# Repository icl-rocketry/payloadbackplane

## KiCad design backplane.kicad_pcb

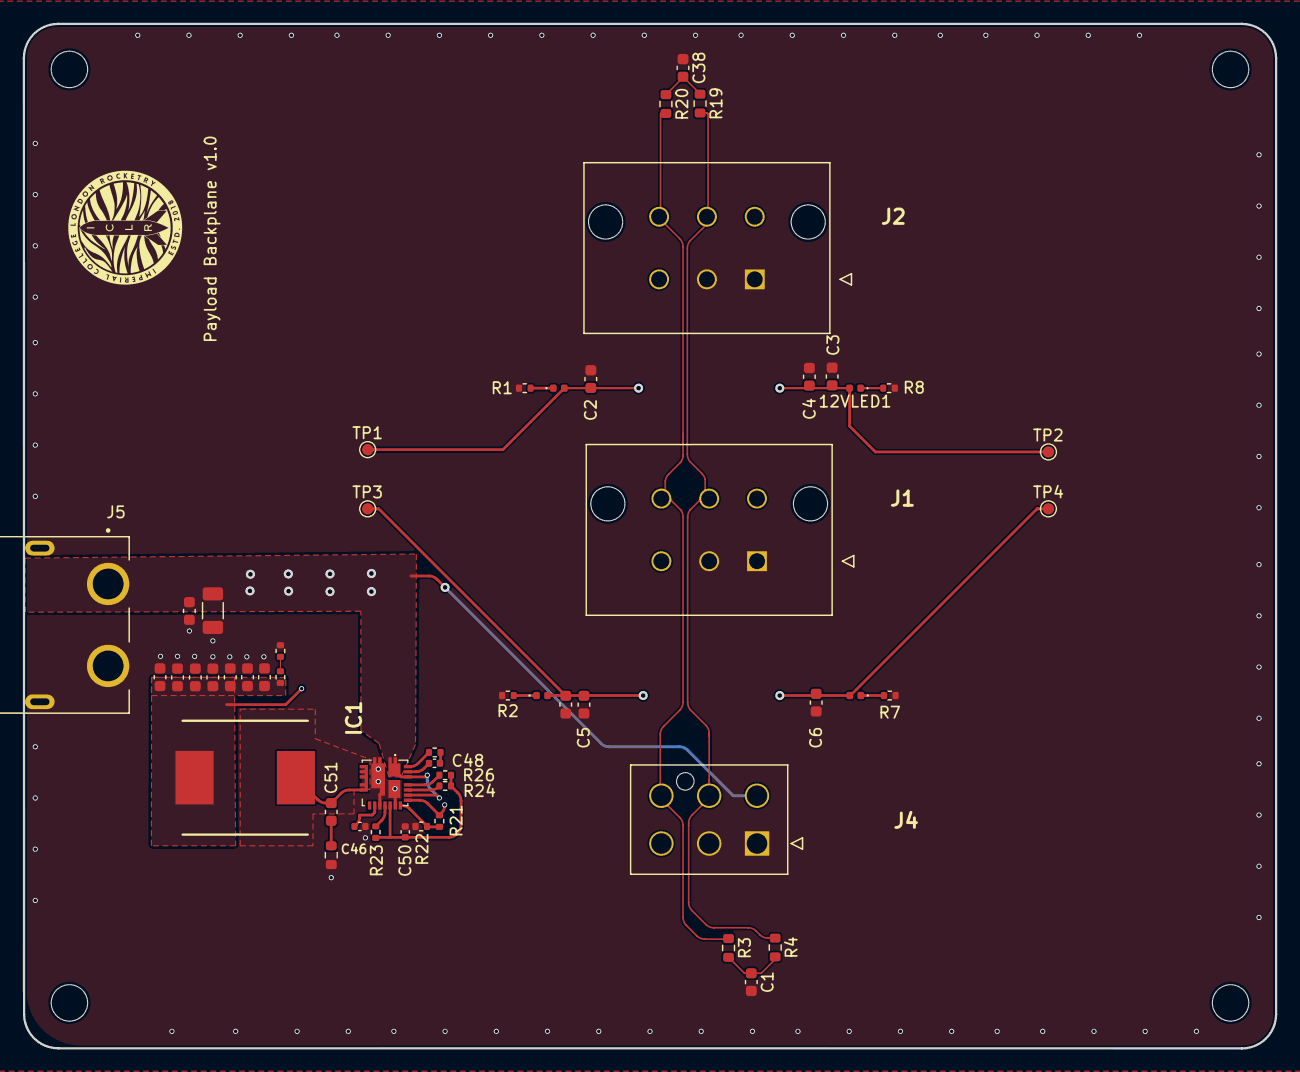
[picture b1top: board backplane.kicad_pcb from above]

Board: 4 copper layers, 110.0 x 90.0 mm, 57 parts (0 on the bottom side), 24 nets.

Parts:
3.3VLED1, 3.3VLED2: 3.3VLED; LED_0402_1005Metric
12VLED1, 12VLED2: 12VLED; LED_0402_1005Metric
C1, C2, C3, C4, C5, C6, C38, C39: C_Small; C_0603_1608Metric
C29, C40, C41, C42, C43, C44, C45: 22uF; C_0603_1608Metric
C46: 4.7uF; C_0402_1005Metric
C47: 47uF; C_1206_3216Metric
C48: 0.1uF; C_0402_1005Metric
C49: 100nF; C_0603_1608Metric
C50: 1uF; C_0402_1005Metric
C51: 680pF; C_0603_1608Metric
H1, H2, H3, H4: MountingHole; MountingHole_3.2mm_M3
IC1: SiC437AED-T1-GE3; SiC437BEDT1GE3
J1, J2: 46010-0622; 46010-06YY
J4: 212520-1006
J5: XT60PW-F; AMASS_XT60PW-F
L3: SRP1050WA-3R3M; INDPM110100X540N
LOGO1: ICLR LOGO; iclr_logo_estd2018_10mm
R1, R2, R7, R8: 1k; R_0402_1005Metric
R3, R4, R19, R20: 60.4; R_0603_1608Metric
R5, R22, R23: 10k; R_0402_1005Metric
R6: 160k; R_0402_1005Metric
R21: 45k; R_0402_1005Metric
R24: 51k; R_0402_1005Metric
R25: 2.2; R_0402_1005Metric
R26: 100k; R_0402_1005Metric
R27: 5.1; R_0603_1608Metric
TP1, TP2, TP3, TP4: TestPoint; TestPoint_Pad_D1.0mm

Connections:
+3.3V: 3.3VLED1.2 (A), 3.3VLED2.2 (A), C2.1, C5.1, C39.1, J1.3, J2.3, J4.3, TP1.1, TP3.1
+12V: 12VLED1.2 (A), 12VLED2.2 (A), C3.2, C4.2, C6.2, C47.1, C49.1, IC1.1 (V_IN_1), IC1.2 (V_IN_2), IC1.19 (EN), IC1.22 (VIN_1), IC1.26 (VIN_2), J1.4, J2.4, J4.4, J5.1, TP2.1, TP4.1
/buckC/BOOT: C48.1, IC1.23 (BOOT)
/buckC/FB: IC1.17 (FB), R21.1, R22.1
/buckC/MODE_1: IC1.21 (_MODE_1), R24.2
/buckC/MODE_2: IC1.20 (MODE_2), R26.1
/buckC/PHASE: IC1.24 (PHASE), R25.1
/buckC/SW: C51.1, IC1.5 (SW_1), IC1.6 (SW_2), IC1.7 (SW_3), IC1.8 (SW_4), IC1.9 (SW_5), IC1.30 (SW_6), L3.2
/buckC/Vdd: C50.2, IC1.15 (VDD), R23.1, R24.1, R26.2
CAN_H: J1.6, J2.6, J4.6, R3.1, R20.2
CAN_L: J1.5, J2.5, J4.5, R4.1, R19.2
GND: C1.2, C2.2, C3.1, C4.1, C5.2, C6.1, C29.1, C38.1, C39.2, C40.1, C41.1, C42.1, C43.1, C44.1, C45.1, C46.2, C47.2, C49.2, C50.1, IC1.3 (P_GND_1), IC1.4 (P_GND_2), IC1.13 (P_GND_3), IC1.16 (A_GND), IC1.25 (AGND), IC1.27 (PGND), IC1.29 (P_GND_4), J1.1, J1.2, J2.1, J2.2, J4.1, J4.2, J5.2, J5.S1 (SHIELD), J5.S2 (SHIELD), R1.1, R2.1, R6.2, R7.1, R8.1, R22.2, R27.2
unnamed: 3.3VLED1.1 (K), R1.2
unnamed: 3.3VLED2.1 (K), R2.2
unnamed: 12VLED1.1 (K), R8.2
unnamed: 12VLED2.1 (K), R7.2
unnamed: C1.1, R3.2, R4.2
unnamed: C38.2, R19.1, R20.1
unnamed: C48.2, R25.2
unnamed: C51.2, R27.1
unnamed: IC1.14 (P_GOOD), R23.2
unnamed: C46.1, IC1.12 (V_DRV)
unnamed: R5.2, R6.1
RBUS_uC_V: C29.2, C40.2, C41.2, C42.2, C43.2, C44.2, C45.2, IC1.18 (V_OUT), L3.1, R5.1, R21.2

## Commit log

2024-03-14 initial commit
    hi Soham
2024-05-18 Overhaul of design
    Changed out the SFMC Oresat connectors for the 46010-0622 Molex; added the SC4215; reduced from 4 connectors to three connectors - no changes made to the footprint, changes only made to the schematic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
2024-05-30 Configuring stuff
    wires and zones added - will change to Si438 + add a switch at some point + some mistakes to still iron out
2024-05-30 neatened things
    leds
2024-05-31 reducing more DRCs
    zone violations etc
2024-05-31 resolving more violations
    connections etc
2024-05-31 10 more to go
    DRC reduction
2024-06-02 more changes
2024-06-02 figuring things out
2024-06-02 more drcs out
    last error is naming convention - after will neaten everything up + add a switch then should be done
2024-06-03 filleted
    to add switches then next review
2024-06-07 review overview
    half of them sent
2024-06-07 changes
    soham
2024-08-07 made changes
    moved some things
2024-08-08 silkscreen
